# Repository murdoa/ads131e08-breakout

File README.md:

# ADS131E08 - Breakout

### Summary
Breakout board for bipolar 24-bit 8 channel simultaneous sampling ADC. 
Boards are daisy chainable for expanded inputs up to 128 input. Input range +/- 2.4V. PMOD compatible SPI Interface.

#### Features:
 - Daisy Chainable Design
 - External Clock Input
 - Configurble Active / Passive Frontend
 - Frontend Op-amps TLV4333 - 2uV Vos, 0.02 uV/C
 - Input Range -2.4V to 2.4V
 - Resolution 24 bit
 - Max sampling speeds 8ksps @ 24 bit, 32 ksps @ 16 bit
 
## Rendered Board

## Silkscreen and Component Layout

## Copper Layers
| Top Copper | Bottom Copper |
|:----:|:----:|
||  |

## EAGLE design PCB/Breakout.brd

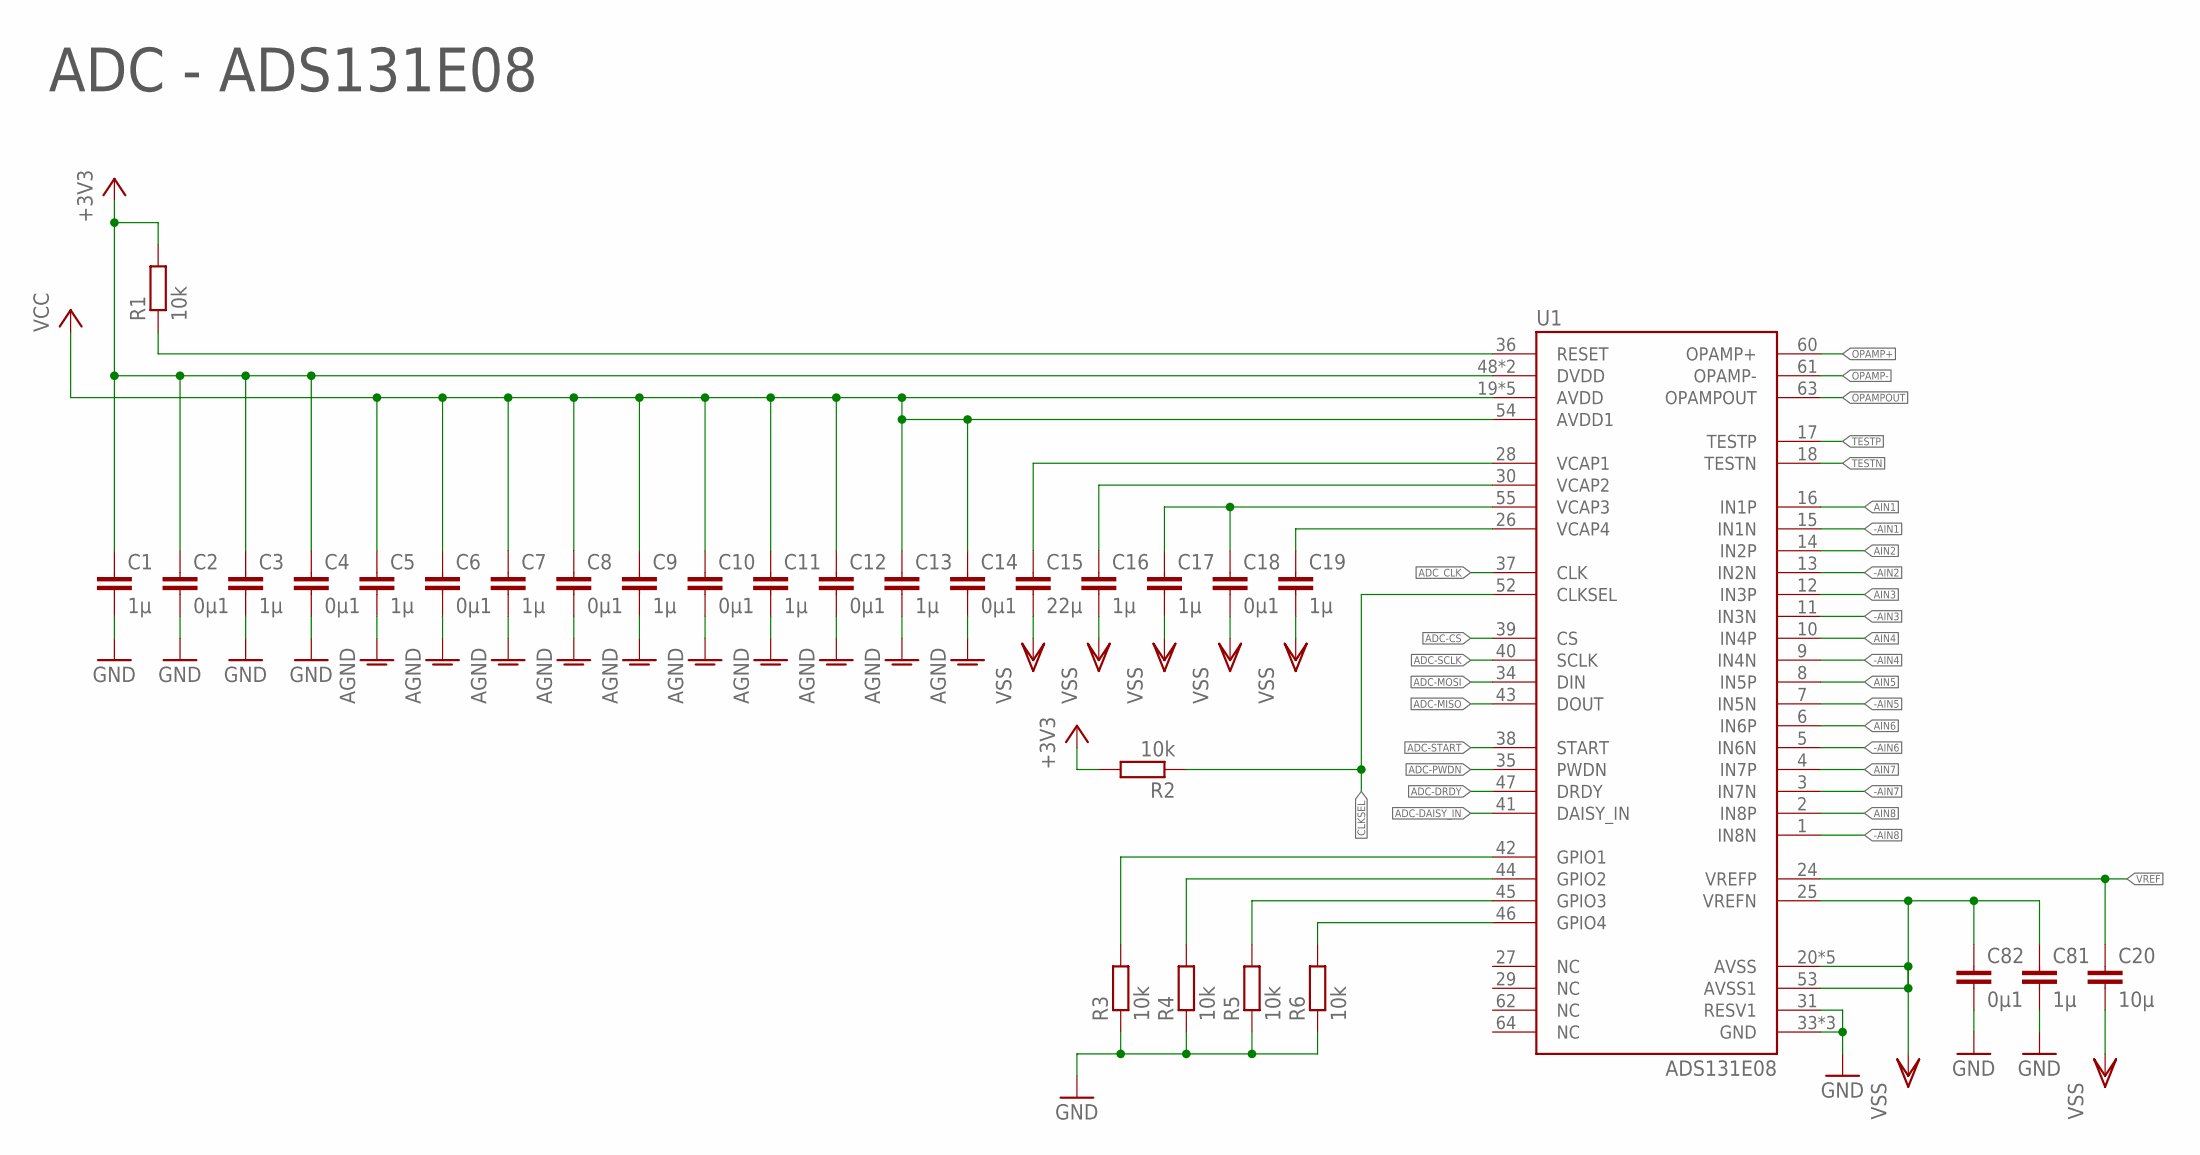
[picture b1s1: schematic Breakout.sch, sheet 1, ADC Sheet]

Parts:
C1, C3, C5, C7, C9, C11, C13, C16, C17, C19, C81: 1µ; C0603
C2, C4, C6, C8, C10, C12, C14, C18, C82: 0µ1; C0603
C15: 22µ; C0603
C20: 10µ; C0603
R1, R2, R3, R4, R5, R6: 10k; R0603
U1: ADS131E08; TQFP-64

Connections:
+3V3: C1.1, C2.1, C3.1, C4.1, R1.2, R2.2, U1.48 (DVDD), U1.50 (DVDD); also elsewhere on the board
-AIN1: U1.15 (IN1N); also elsewhere on the board
-AIN2: U1.13 (IN2N); also elsewhere on the board
-AIN3: U1.11 (IN3N); also elsewhere on the board
-AIN4: U1.9 (IN4N); also elsewhere on the board
-AIN5: U1.7 (IN5N); also elsewhere on the board
-AIN6: U1.5 (IN6N); also elsewhere on the board
-AIN7: U1.3 (IN7N); also elsewhere on the board
-AIN8: U1.1 (IN8N); also elsewhere on the board
ADC-CS: U1.39 (CS); also elsewhere on the board
ADC-DAISY_IN: U1.41 (DAISY_IN); also elsewhere on the board
ADC-DRDY: U1.47 (DRDY); also elsewhere on the board
ADC-MISO: U1.43 (DOUT); also elsewhere on the board
ADC-MOSI: U1.34 (DIN); also elsewhere on the board
ADC-PWDN: U1.35 (PWDN); also elsewhere on the board
ADC-RST: R1.1, U1.36 (RESET); also elsewhere on the board
ADC-SCLK: U1.40 (SCLK); also elsewhere on the board
ADC-START: U1.38 (START); also elsewhere on the board
ADC_CLK: U1.37 (CLK); also elsewhere on the board
AIN1: U1.16 (IN1P); also elsewhere on the board
AIN2: U1.14 (IN2P); also elsewhere on the board
AIN3: U1.12 (IN3P); also elsewhere on the board
AIN4: U1.10 (IN4P); also elsewhere on the board
AIN5: U1.8 (IN5P); also elsewhere on the board
AIN6: U1.6 (IN6P); also elsewhere on the board
AIN7: U1.4 (IN7P); also elsewhere on the board
AIN8: U1.2 (IN8P); also elsewhere on the board
CLKSEL: R2.1, U1.52 (CLKSEL)
GND: C1.2, C2.2, C3.2, C4.2, C5.2, C6.2, C7.2, C8.2, C9.2, C10.2, C11.2, C12.2, C13.2, C14.2, C81.2, C82.2, R3.1, R4.1, R5.1, R6.1, U1.31 (RESV1), U1.33 (GND), U1.49 (GND), U1.51 (GND); also elsewhere on the board
GPIO1: R3.2, U1.42 (GPIO1); also elsewhere on the board
GPIO2: R4.2, U1.44 (GPIO2)
GPIO3: R5.2, U1.45 (GPIO3)
GPIO4: R6.2, U1.46 (GPIO4)
OPAMP+: U1.60 (OPAMP+)
OPAMP-: U1.61 (OPAMP-)
OPAMPOUT: U1.63 (OPAMPOUT)
TESTN: U1.18 (TESTN)
TESTP: U1.17 (TESTP)
VCAP1: C15.1, U1.28 (VCAP1)
VCAP2: C16.1, U1.30 (VCAP2)
VCAP3: C17.1, C18.1, U1.55 (VCAP3)
VCAP4: C19.1, U1.26 (VCAP4)
VCC: C5.1, C6.1, C7.1, C8.1, C9.1, C10.1, C11.1, C12.1, C13.1, C14.1, U1.19 (AVDD), U1.21 (AVDD), U1.22 (AVDD), U1.54 (AVDD1), U1.56 (AVDD), U1.59 (AVDD); also elsewhere on the board
VREF: C20.1, U1.24 (VREFP); also elsewhere on the board
VSS: C15.2, C16.2, C17.2, C18.2, C19.2, C20.2, C81.1, C82.1, U1.20 (AVSS), U1.23 (AVSS), U1.25 (VREFN), U1.32 (AVSS), U1.53 (AVSS1), U1.57 (AVSS), U1.58 (AVSS); also elsewhere on the board

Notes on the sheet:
ADC - ADS131E08

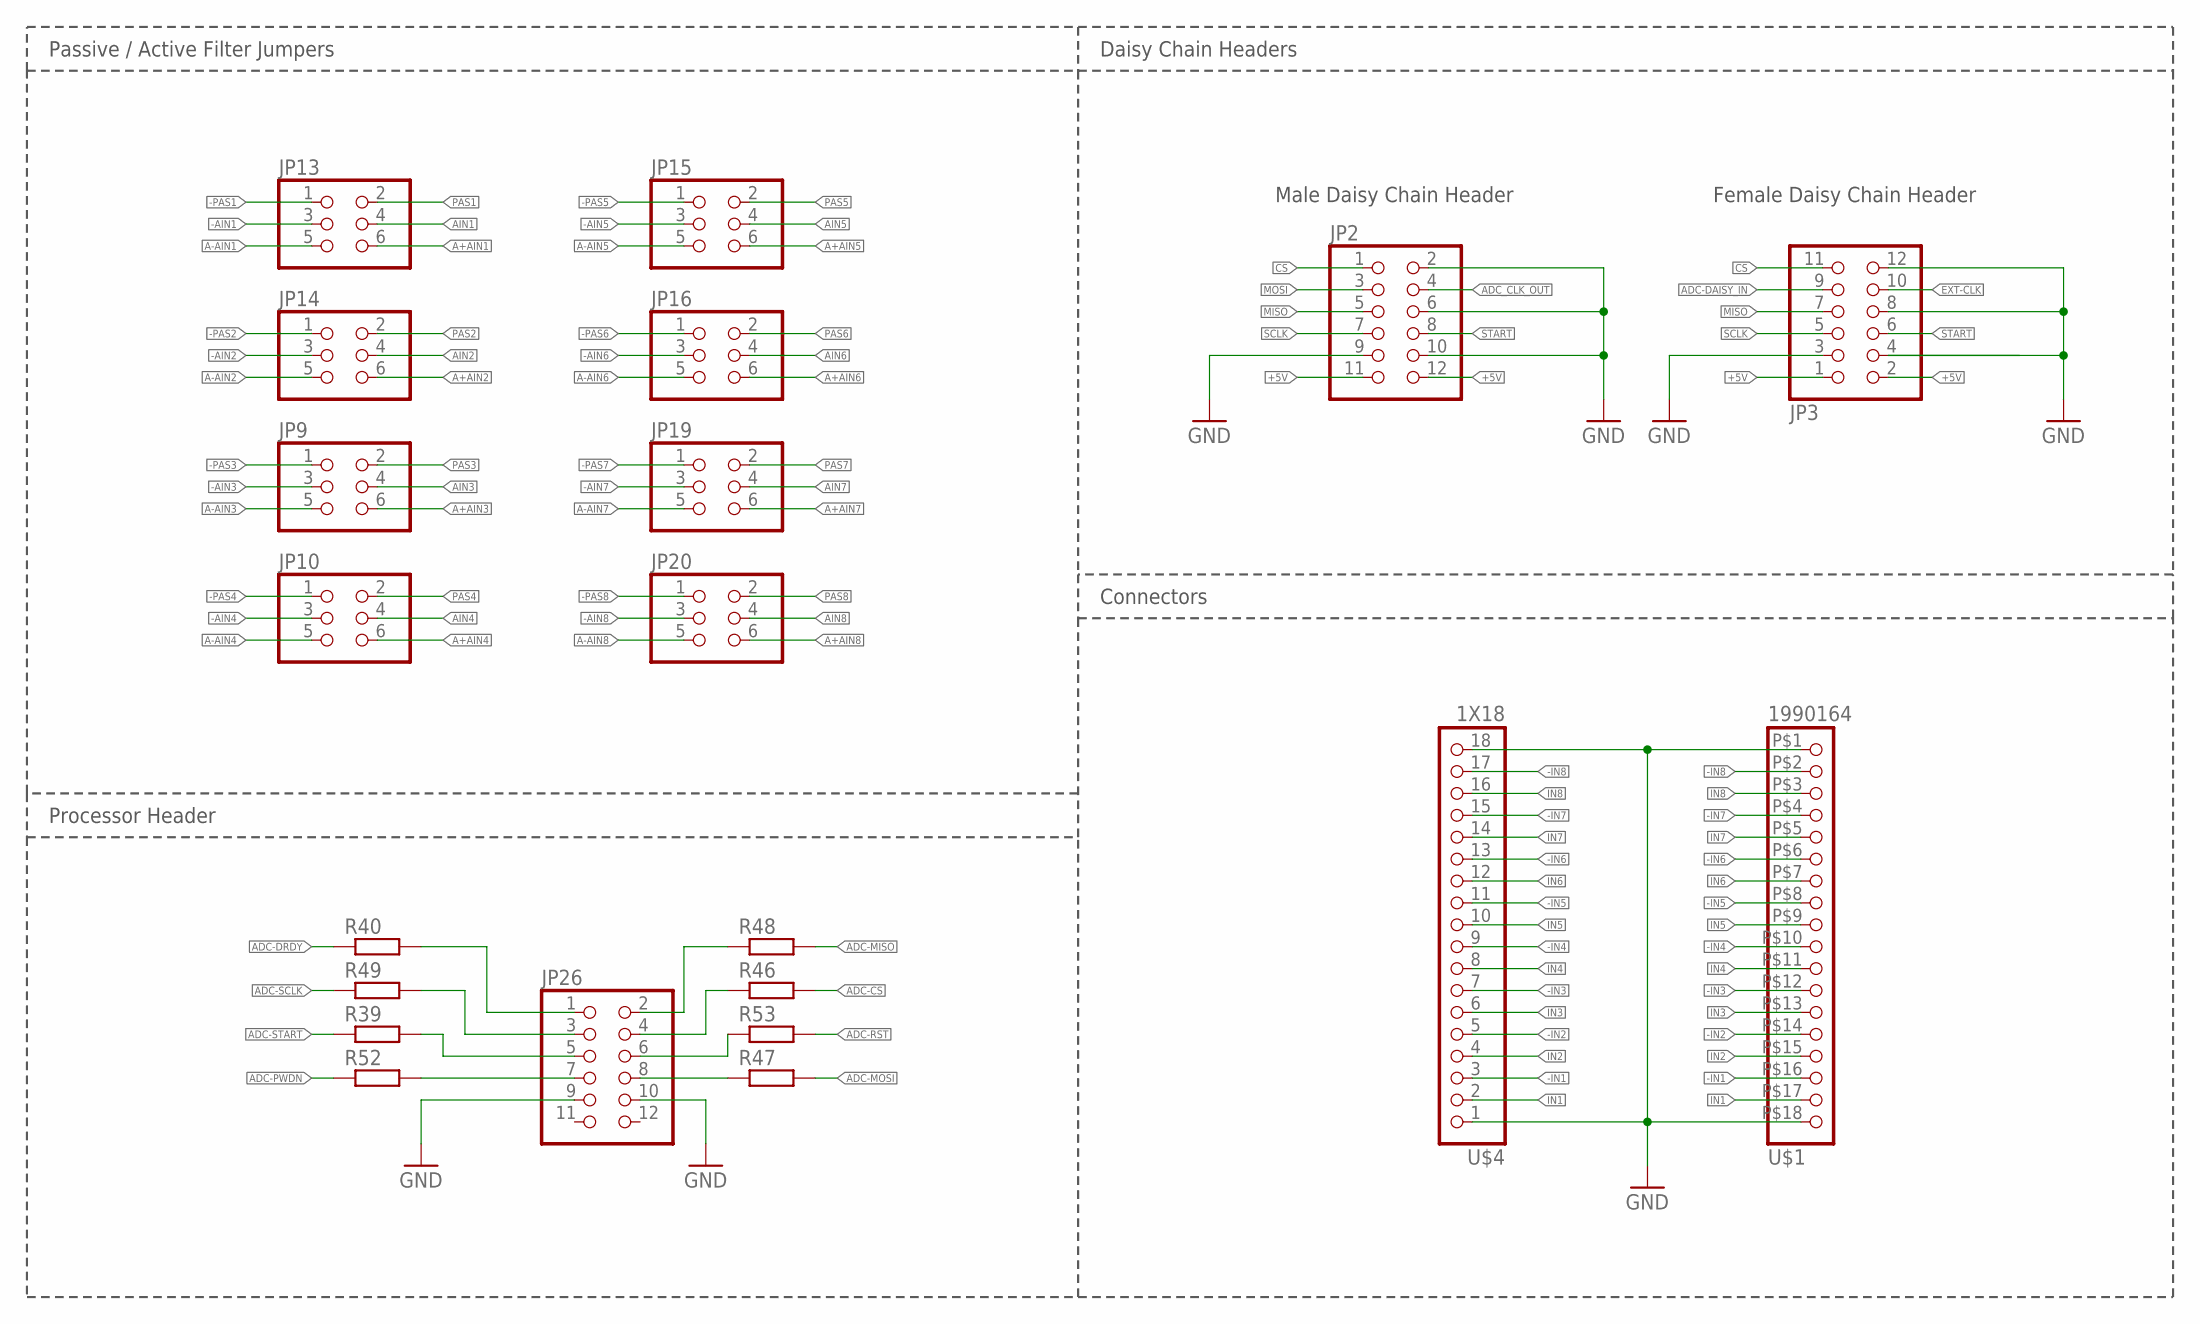
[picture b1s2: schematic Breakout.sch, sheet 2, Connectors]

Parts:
JP2, JP3, JP26: PINHD-2X6/90; 2X06/90
JP9, JP10, JP13, JP14, JP15, JP16, JP19, JP20: PINHD-2X3; 2X03
R39, R40, R46, R47, R48, R49, R52, R53: R-EU_R0603; R0603
U$1: 1990164; PTSA-2.5-Z
U$4: 1X18; 1X18/90

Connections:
+5V: JP2.11, JP2.12, JP3.1, JP3.2; also elsewhere on the board
-AIN1: JP13.3; also elsewhere on the board
-AIN2: JP14.3; also elsewhere on the board
-AIN3: JP9.3; also elsewhere on the board
-AIN4: JP10.3; also elsewhere on the board
-AIN5: JP15.3; also elsewhere on the board
-AIN6: JP16.3; also elsewhere on the board
-AIN7: JP19.3; also elsewhere on the board
-AIN8: JP20.3; also elsewhere on the board
-IN1: U$1.P$16 (3), U$4.3; also elsewhere on the board
-IN2: U$1.P$14 (5), U$4.5; also elsewhere on the board
-IN3: U$1.P$12 (7), U$4.7; also elsewhere on the board
-IN4: U$1.P$10 (9), U$4.9; also elsewhere on the board
-IN5: U$1.P$8 (11), U$4.11; also elsewhere on the board
-IN6: U$1.P$6 (13), U$4.13; also elsewhere on the board
-IN7: U$1.P$4 (15), U$4.15; also elsewhere on the board
-IN8: U$1.P$2 (17), U$4.17; also elsewhere on the board
-PAS1: JP13.1; also elsewhere on the board
-PAS2: JP14.1; also elsewhere on the board
-PAS3: JP9.1; also elsewhere on the board
-PAS4: JP10.1; also elsewhere on the board
-PAS5: JP15.1; also elsewhere on the board
-PAS6: JP16.1; also elsewhere on the board
-PAS7: JP19.1; also elsewhere on the board
-PAS8: JP20.1; also elsewhere on the board
A+AIN1: JP13.6; also elsewhere on the board
A+AIN2: JP14.6; also elsewhere on the board
A+AIN3: JP9.6; also elsewhere on the board
A+AIN4: JP10.6; also elsewhere on the board
A+AIN5: JP15.6; also elsewhere on the board
A+AIN6: JP16.6; also elsewhere on the board
A+AIN7: JP19.6; also elsewhere on the board
A+AIN8: JP20.6; also elsewhere on the board
A-AIN1: JP13.5; also elsewhere on the board
A-AIN2: JP14.5; also elsewhere on the board
A-AIN3: JP9.5; also elsewhere on the board
A-AIN4: JP10.5; also elsewhere on the board
A-AIN5: JP15.5; also elsewhere on the board
A-AIN6: JP16.5; also elsewhere on the board
A-AIN7: JP19.5; also elsewhere on the board
A-AIN8: JP20.5; also elsewhere on the board
ADC-CS: R46.1; also elsewhere on the board
ADC-DAISY_IN: JP3.9; also elsewhere on the board
ADC-DRDY: R40.2; also elsewhere on the board
ADC-MISO: R48.1; also elsewhere on the board
ADC-MOSI: R47.1; also elsewhere on the board
ADC-PWDN: R52.2; also elsewhere on the board
ADC-RST: R53.2; also elsewhere on the board
ADC-SCLK: R49.1; also elsewhere on the board
ADC-START: R39.2; also elsewhere on the board
ADC_CLK_OUT: JP2.4; also elsewhere on the board
AIN1: JP13.4; also elsewhere on the board
AIN2: JP14.4; also elsewhere on the board
AIN3: JP9.4; also elsewhere on the board
AIN4: JP10.4; also elsewhere on the board
AIN5: JP15.4; also elsewhere on the board
AIN6: JP16.4; also elsewhere on the board
AIN7: JP19.4; also elsewhere on the board
AIN8: JP20.4; also elsewhere on the board
CS: JP2.1, JP3.11, JP26.4, R46.2
DRDY: JP26.1, R40.1
EXT-CLK: JP3.10; also elsewhere on the board
GND: JP2.2, JP2.6, JP2.9, JP2.10, JP3.3, JP3.4, JP3.8, JP3.12, JP26.9, JP26.10, U$1.P$1 (18), U$1.P$18 (1), U$4.1, U$4.18; also elsewhere on the board
IN1: U$1.P$17 (2), U$4.2; also elsewhere on the board
IN2: U$1.P$15 (4), U$4.4; also elsewhere on the board
IN3: U$1.P$13 (6), U$4.6; also elsewhere on the board
IN4: U$1.P$11 (8), U$4.8; also elsewhere on the board
IN5: U$1.P$9 (10), U$4.10; also elsewhere on the board
IN6: U$1.P$7 (12), U$4.12; also elsewhere on the board
IN7: U$1.P$5 (14), U$4.14; also elsewhere on the board
IN8: U$1.P$3 (16), U$4.16; also elsewhere on the board
MISO: JP2.5, JP3.7, JP26.2, R48.2
MOSI: JP2.3, JP26.8, R47.2
PAS1: JP13.2; also elsewhere on the board
PAS2: JP14.2; also elsewhere on the board
PAS3: JP9.2; also elsewhere on the board
PAS4: JP10.2; also elsewhere on the board
PAS5: JP15.2; also elsewhere on the board
PAS6: JP16.2; also elsewhere on the board
PAS7: JP19.2; also elsewhere on the board
PAS8: JP20.2; also elsewhere on the board
PWDN: JP26.7, R52.1
RST: JP26.6, R53.1
SCLK: JP2.7, JP3.5, JP26.3, R49.2
START: JP2.8, JP3.6, JP26.5, R39.1

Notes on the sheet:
Processor Header
Male Daisy Chain Header
Female Daisy Chain Header
Passive / Active Filter Jumpers
Daisy Chain Headers
Connectors

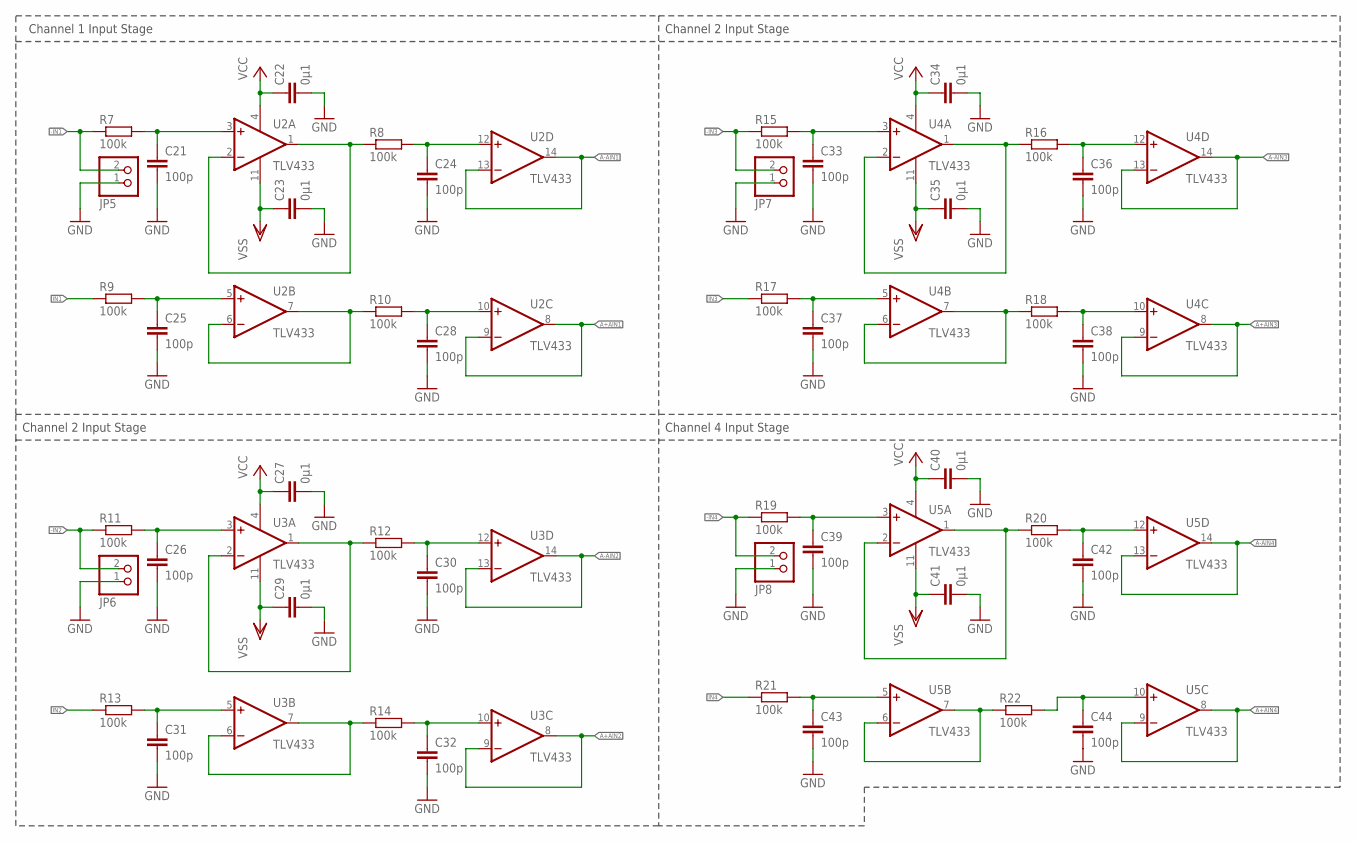
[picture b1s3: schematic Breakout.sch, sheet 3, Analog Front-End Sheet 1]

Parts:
C21, C24, C25, C26, C28, C30, C31, C32, C33, C36, C37, C38, C39, C42, C43, C44: 100p; C0603
C22, C23, C27, C29, C34, C35, C40, C41: 0µ1; C0603
JP5, JP6, JP7, JP8: PINHD-1X2; 1X02
R7, R8, R9, R10, R11, R12, R13, R14, R15, R16, R17, R18, R19, R20, R21, R22: 100k; R0603
U2, U3, U4, U5: TLV433; TSSOP14

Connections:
-IN1: JP5.2, R7.1; also elsewhere on the board
-IN2: JP6.2, R11.1; also elsewhere on the board
-IN3: JP7.2, R15.1; also elsewhere on the board
-IN4: JP8.2, R19.1; also elsewhere on the board
-PAS1: C21.1, R7.2, U2.3 (+IN); also elsewhere on the board
-PAS2: C26.1, R11.2, U3.3 (+IN); also elsewhere on the board
-PAS3: C33.1, R15.2, U4.3 (+IN); also elsewhere on the board
-PAS4: C39.1, R19.2, U5.3 (+IN); also elsewhere on the board
A+AIN1: U2.8 (OUT), U2.9 (-IN); also elsewhere on the board
A+AIN2: U3.8 (OUT), U3.9 (-IN); also elsewhere on the board
A+AIN3: U4.8 (OUT), U4.9 (-IN); also elsewhere on the board
A+AIN4: U5.8 (OUT), U5.9 (-IN); also elsewhere on the board
A-AIN1: U2.13 (-IN), U2.14 (OUT); also elsewhere on the board
A-AIN2: U3.13 (-IN), U3.14 (OUT); also elsewhere on the board
A-AIN3: U4.13 (-IN), U4.14 (OUT); also elsewhere on the board
A-AIN4: U5.13 (-IN), U5.14 (OUT); also elsewhere on the board
GND: C21.2, C22.2, C23.2, C24.2, C25.2, C26.2, C27.2, C28.2, C29.2, C30.2, C31.2, C32.2, C33.2, C34.2, C35.2, C36.2, C37.2, C38.2, C39.2, C40.2, C41.2, C42.2, C43.2, C44.2, JP5.1, JP6.1, JP7.1, JP8.1; also elsewhere on the board
IN1: R9.1; also elsewhere on the board
IN2: R13.1; also elsewhere on the board
IN3: R17.1; also elsewhere on the board
IN4: R21.1; also elsewhere on the board
unnamed: C36.1, R16.2, U4.12 (+IN)
unnamed: R16.1, U4.1 (OUT), U4.2 (-IN)
unnamed: C28.1, R10.2, U2.10 (+IN)
unnamed: C24.1, R8.2, U2.12 (+IN)
unnamed: R8.1, U2.1 (OUT), U2.2 (-IN)
unnamed: R10.1, U2.6 (-IN), U2.7 (OUT)
unnamed: C38.1, R18.2, U4.10 (+IN)
unnamed: C30.1, R12.2, U3.12 (+IN)
unnamed: R12.1, U3.1 (OUT), U3.2 (-IN)
unnamed: R18.1, U4.6 (-IN), U4.7 (OUT)
unnamed: C32.1, R14.2, U3.10 (+IN)
unnamed: R14.1, U3.6 (-IN), U3.7 (OUT)
unnamed: C42.1, R20.2, U5.12 (+IN)
unnamed: R20.1, U5.1 (OUT), U5.2 (-IN)
unnamed: C44.1, R22.2, U5.10 (+IN)
unnamed: R22.1, U5.6 (-IN), U5.7 (OUT)
PAS1: C25.1, R9.2, U2.5 (+IN); also elsewhere on the board
PAS2: C31.1, R13.2, U3.5 (+IN); also elsewhere on the board
PAS3: C37.1, R17.2, U4.5 (+IN); also elsewhere on the board
PAS4: C43.1, R21.2, U5.5 (+IN); also elsewhere on the board
VCC: C22.1, C27.1, C34.1, C40.1, U2.4 (V+), U3.4 (V+), U4.4 (V+), U5.4 (V+); also elsewhere on the board
VSS: C23.1, C29.1, C35.1, C41.1, U2.11 (V-), U3.11 (V-), U4.11 (V-), U5.11 (V-); also elsewhere on the board

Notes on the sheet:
Channel 1 Input Stage
Channel 2 Input Stage
Channel 4 Input Stage

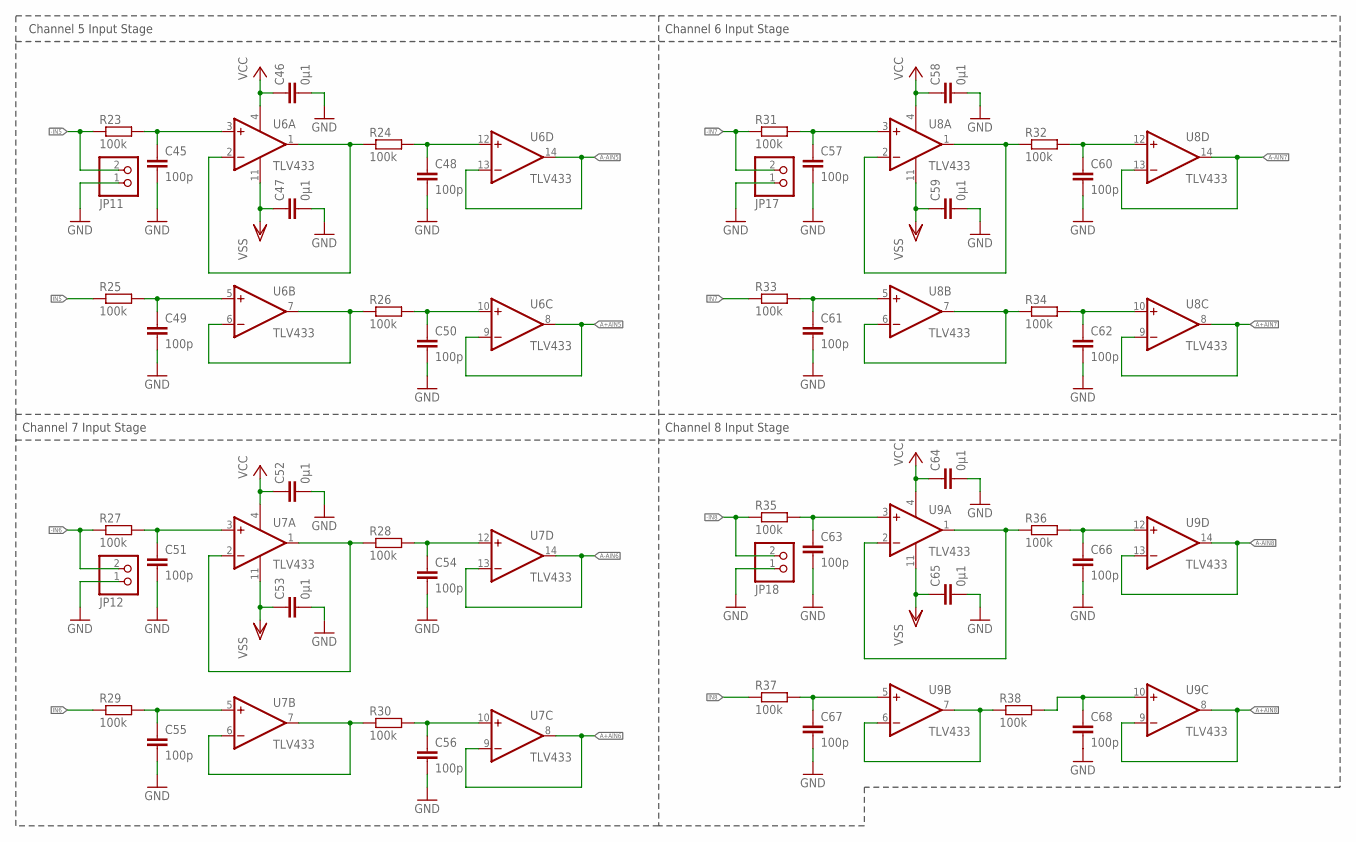
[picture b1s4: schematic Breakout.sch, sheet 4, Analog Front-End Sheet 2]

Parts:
C45, C48, C49, C50, C51, C54, C55, C56, C57, C60, C61, C62, C63, C66, C67, C68: 100p; C0603
C46, C47, C52, C53, C58, C59, C64, C65: 0µ1; C0603
JP11, JP12, JP17, JP18: PINHD-1X2; 1X02
R23, R24, R25, R26, R27, R28, R29, R30, R31, R32, R33, R34, R35, R36, R37, R38: 100k; R0603
U6, U7, U8, U9: TLV433; TSSOP14

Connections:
-IN5: JP11.2, R23.1; also elsewhere on the board
-IN6: JP12.2, R27.1; also elsewhere on the board
-IN7: JP17.2, R31.1; also elsewhere on the board
-IN8: JP18.2, R35.1; also elsewhere on the board
-PAS5: C45.1, R23.2, U6.3 (+IN); also elsewhere on the board
-PAS6: C51.1, R27.2, U7.3 (+IN); also elsewhere on the board
-PAS7: C57.1, R31.2, U8.3 (+IN); also elsewhere on the board
-PAS8: C63.1, R35.2, U9.3 (+IN); also elsewhere on the board
A+AIN5: U6.8 (OUT), U6.9 (-IN); also elsewhere on the board
A+AIN6: U7.8 (OUT), U7.9 (-IN); also elsewhere on the board
A+AIN7: U8.8 (OUT), U8.9 (-IN); also elsewhere on the board
A+AIN8: U9.8 (OUT), U9.9 (-IN); also elsewhere on the board
A-AIN5: U6.13 (-IN), U6.14 (OUT); also elsewhere on the board
A-AIN6: U7.13 (-IN), U7.14 (OUT); also elsewhere on the board
A-AIN7: U8.13 (-IN), U8.14 (OUT); also elsewhere on the board
A-AIN8: U9.13 (-IN), U9.14 (OUT); also elsewhere on the board
GND: C45.2, C46.2, C47.2, C48.2, C49.2, C50.2, C51.2, C52.2, C53.2, C54.2, C55.2, C56.2, C57.2, C58.2, C59.2, C60.2, C61.2, C62.2, C63.2, C64.2, C65.2, C66.2, C67.2, C68.2, JP11.1, JP12.1, JP17.1, JP18.1; also elsewhere on the board
IN5: R25.1; also elsewhere on the board
IN6: R29.1; also elsewhere on the board
IN7: R33.1; also elsewhere on the board
IN8: R37.1; also elsewhere on the board
unnamed: C48.1, R24.2, U6.12 (+IN)
unnamed: R24.1, U6.1 (OUT), U6.2 (-IN)
unnamed: C50.1, R26.2, U6.10 (+IN)
unnamed: R26.1, U6.6 (-IN), U6.7 (OUT)
unnamed: C54.1, R28.2, U7.12 (+IN)
unnamed: R28.1, U7.1 (OUT), U7.2 (-IN)
unnamed: C56.1, R30.2, U7.10 (+IN)
unnamed: R30.1, U7.6 (-IN), U7.7 (OUT)
unnamed: C60.1, R32.2, U8.12 (+IN)
unnamed: R32.1, U8.1 (OUT), U8.2 (-IN)
unnamed: C62.1, R34.2, U8.10 (+IN)
unnamed: R34.1, U8.6 (-IN), U8.7 (OUT)
unnamed: C66.1, R36.2, U9.12 (+IN)
unnamed: R36.1, U9.1 (OUT), U9.2 (-IN)
unnamed: C68.1, R38.2, U9.10 (+IN)
unnamed: R38.1, U9.6 (-IN), U9.7 (OUT)
PAS5: C49.1, R25.2, U6.5 (+IN); also elsewhere on the board
PAS6: C55.1, R29.2, U7.5 (+IN); also elsewhere on the board
PAS7: C61.1, R33.2, U8.5 (+IN); also elsewhere on the board
PAS8: C67.1, R37.2, U9.5 (+IN); also elsewhere on the board
VCC: C46.1, C52.1, C58.1, C64.1, U6.4 (V+), U7.4 (V+), U8.4 (V+), U9.4 (V+); also elsewhere on the board
VSS: C47.1, C53.1, C59.1, C65.1, U6.11 (V-), U7.11 (V-), U8.11 (V-), U9.11 (V-); also elsewhere on the board

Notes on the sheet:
Channel 5 Input Stage
Channel 7 Input Stage
Channel 6 Input Stage
Channel 8 Input Stage

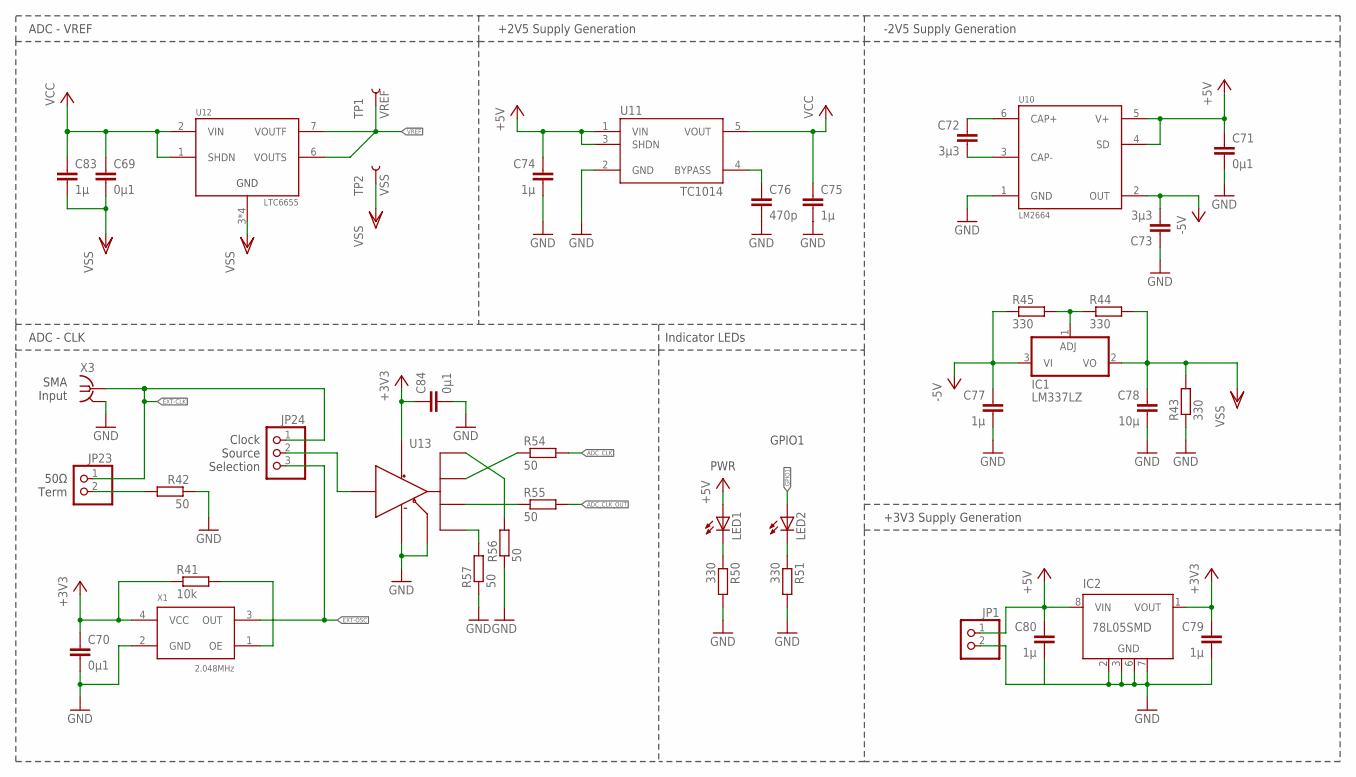
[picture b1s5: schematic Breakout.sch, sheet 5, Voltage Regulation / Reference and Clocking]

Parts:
C69, C70, C71, C84: 0µ1; C0603
C72, C73: 3µ3; C0805
C74, C75, C77, C79, C80: 1µ; C0805
C76: 470p; C0603
C78: 10µ; C0805
C83: 1µ; C0603
IC1: LM337LZ; TO92
IC2: 78L05SMD; SO08
JP1, JP23: PINHD-1X2; 1X02
JP24: PINHD-1X3; 1X03
LED1, LED2: LEDCHIP-LED0805; CHIP-LED0805
R41: 10k; R0603
R42, R54, R55, R56, R57: 50; R0603
R43, R44, R45, R50, R51: 330; R0603
TP1: VREF; PAD.03X.03
TP2: VSS; PAD.03X.03
U10: LM2664; SOT23-6
U11: TC1014; SOT23-5L
U12: LTC6655; LS8
U13: 74AVC9112GTX; XFDFN-8
X1: 2.048MHz; SG5032CAN
X3: BU-SMA-V

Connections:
+3V3: C70.1, C79.1, C84.1, IC2.1 (VOUT), R41.1, U13.P$1 (VCC), X1.4 (VCC); also elsewhere on the board
+5V: C71.1, C74.1, C80.1, IC2.8 (VIN), JP1.1, LED1.A, U10.4 (SD), U10.5 (V+), U11.1 (VIN), U11.3 (SHDN); also elsewhere on the board
-5V: C73.2, C77.1, IC1.3 (VI), R45.1, U10.2 (OUT)
ADC_CLK: R54.2; also elsewhere on the board
ADC_CLK_OUT: R55.2; also elsewhere on the board
EXT-CLK: JP23.1, JP24.1, X3.1; also elsewhere on the board
EXT-OSC: JP24.3, X1.3 (OUT)
GND: C70.2, C71.2, C73.1, C74.2, C75.2, C76.2, C77.2, C78.2, C79.2, C80.2, C84.2, IC2.2 (GND), IC2.3 (GND), IC2.6 (GND), IC2.7 (GND), JP1.2, R42.1, R43.1, R50.2, R51.2, R56.1, R57.1, U10.1 (GND), U11.2 (GND), U13.P$3 (OE), U13.P$4 (GND), X1.2 (GND), X3.2, X3.3 (2), X3.4 (2), X3.5 (2); also elsewhere on the board
GPIO1: LED2.A; also elsewhere on the board
unnamed: R41.2, X1.1 (OE)
unnamed: C72.1, U10.6 (CAP+)
unnamed: C72.2, U10.3 (CAP-)
unnamed: JP24.2, U13.P$2 (A)
unnamed: JP23.2, R42.2
unnamed: C76.1, U11.4 (BYPASS)
unnamed: IC1.1 (ADJ), R44.1, R45.2
unnamed: R54.1, U13.P$6 (Y2)
unnamed: R55.1, U13.P$7 (Y3)
unnamed: R56.2, U13.P$5 (Y1)
unnamed: R57.2, U13.P$8 (Y4)
unnamed: LED2.C, R51.1
unnamed: LED1.C, R50.1
VCC: C69.1, C75.1, C83.1, U11.5 (VOUT), U12.1 (SHDN), U12.2 (VIN); also elsewhere on the board
VREF: TP1.P$1, U12.6 (VOUTS), U12.7 (VOUTF); also elsewhere on the board
VSS: C69.2, C78.1, C83.2, IC1.2 (VO), R43.2, R44.2, TP2.P$1, U12.3 (GND), U12.4 (GND), U12.5 (GND), U12.8 (GND); also elsewhere on the board

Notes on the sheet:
PWR
GPIO1
ADC - VREF
+2V5 Supply Generation
ADC - CLK
50Ω Term
SMA Input
Clock Source Selection
-2V5 Supply Generation
Indicator LEDs
+3V3 Supply Generation

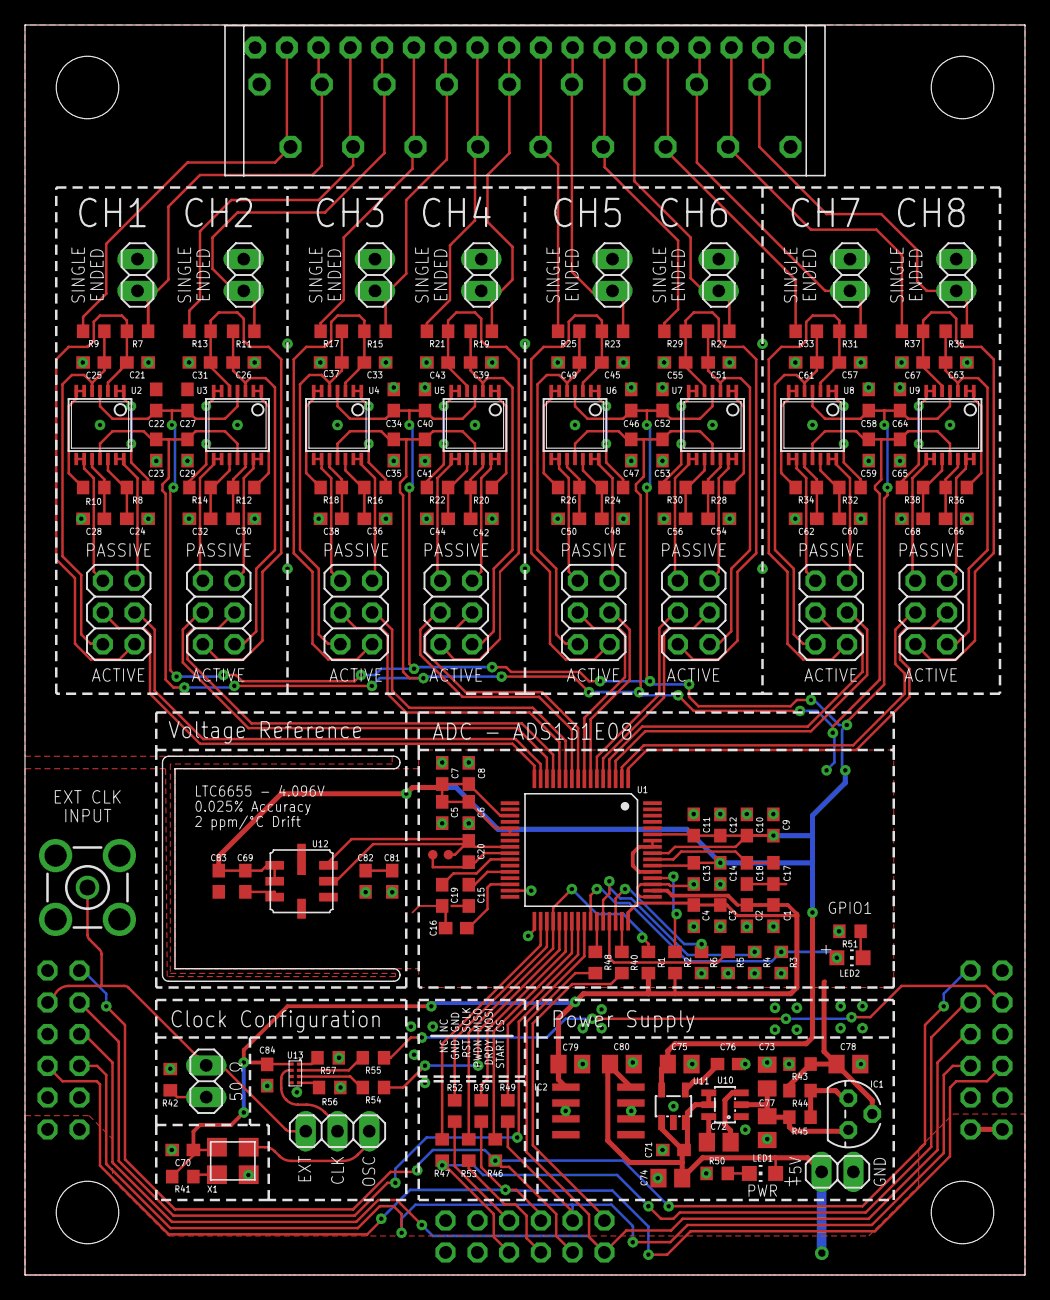
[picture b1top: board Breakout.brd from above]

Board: 2 copper layers, 79.9 x 99.9 mm, 186 parts (0 on the bottom side), 146 nets.

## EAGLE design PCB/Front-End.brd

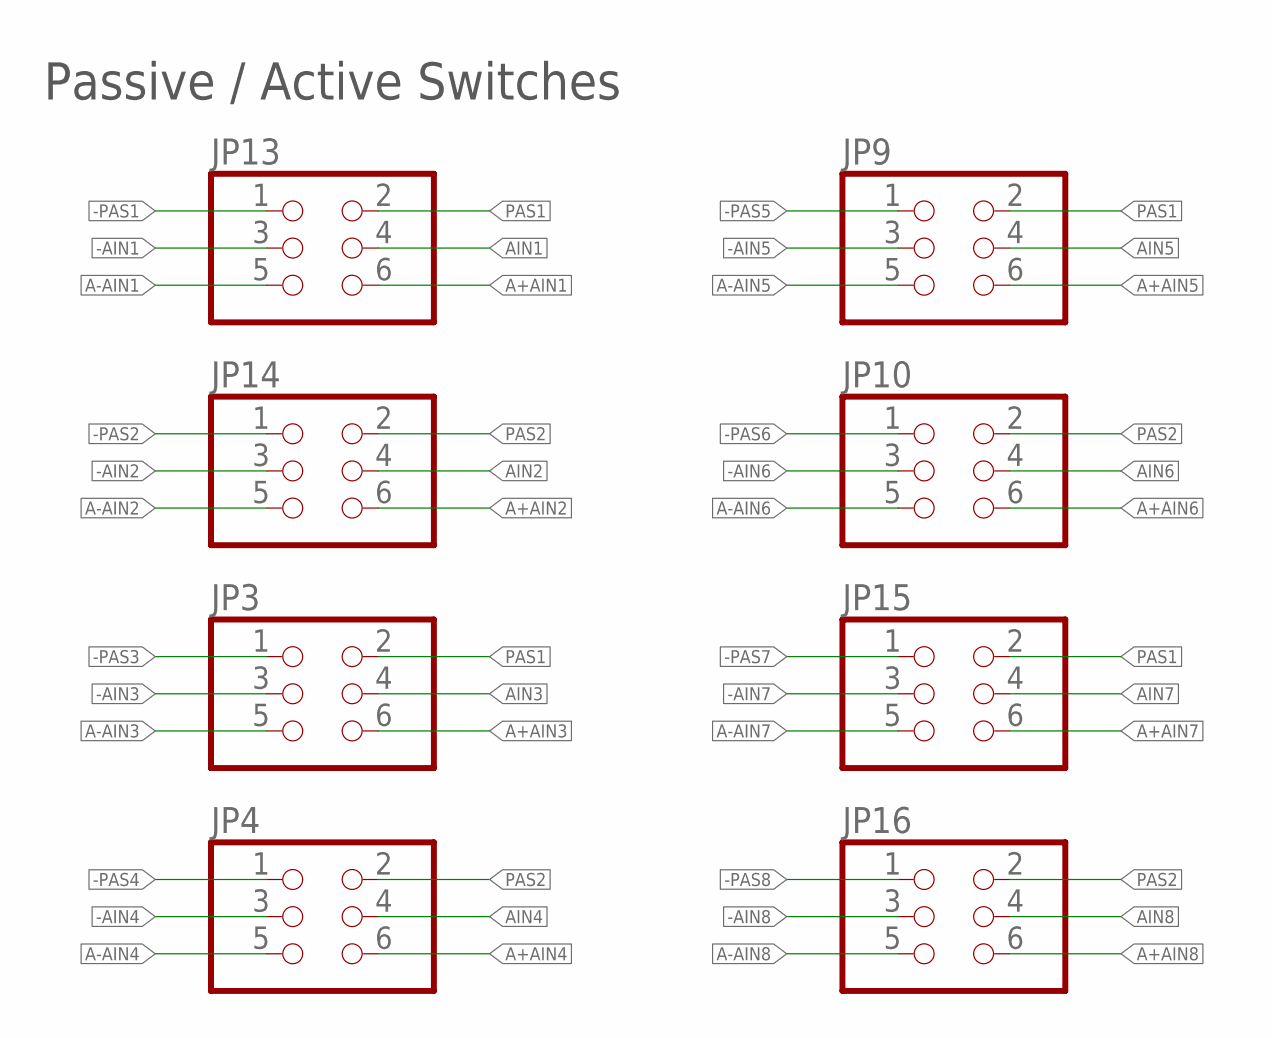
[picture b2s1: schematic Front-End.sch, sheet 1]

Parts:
JP3, JP4, JP9, JP10, JP13, JP14, JP15, JP16: PINHD-2X3; 2X03

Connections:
-AIN1: JP13.3
-AIN2: JP14.3
-AIN3: JP3.3
-AIN4: JP4.3
-AIN5: JP9.3
-AIN6: JP10.3
-AIN7: JP15.3
-AIN8: JP16.3
-PAS1: JP13.1; also elsewhere on the board
-PAS2: JP14.1; also elsewhere on the board
-PAS3: JP3.1; also elsewhere on the board
-PAS4: JP4.1; also elsewhere on the board
-PAS5: JP9.1; also elsewhere on the board
-PAS6: JP10.1; also elsewhere on the board
-PAS7: JP15.1; also elsewhere on the board
-PAS8: JP16.1; also elsewhere on the board
A+AIN1: JP13.6; also elsewhere on the board
A+AIN2: JP14.6; also elsewhere on the board
A+AIN3: JP3.6; also elsewhere on the board
A+AIN4: JP4.6; also elsewhere on the board
A+AIN5: JP9.6; also elsewhere on the board
A+AIN6: JP10.6; also elsewhere on the board
A+AIN7: JP15.6; also elsewhere on the board
A+AIN8: JP16.6; also elsewhere on the board
A-AIN1: JP13.5; also elsewhere on the board
A-AIN2: JP14.5; also elsewhere on the board
A-AIN3: JP3.5; also elsewhere on the board
A-AIN4: JP4.5; also elsewhere on the board
A-AIN5: JP9.5; also elsewhere on the board
A-AIN6: JP10.5; also elsewhere on the board
A-AIN7: JP15.5; also elsewhere on the board
A-AIN8: JP16.5; also elsewhere on the board
AIN1: JP13.4
AIN2: JP14.4
AIN3: JP3.4
AIN4: JP4.4
AIN5: JP9.4
AIN6: JP10.4
AIN7: JP15.4
AIN8: JP16.4
PAS1: JP3.2, JP9.2, JP13.2, JP15.2; also elsewhere on the board
PAS2: JP4.2, JP10.2, JP14.2, JP16.2; also elsewhere on the board

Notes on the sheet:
Passive / Active Switches

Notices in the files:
parts and their libraries:
SparkFun-Aesthetics: Licensing: Creative Commons ShareAlike 4.0 International - https://creativecommons.org/licenses/by-sa/4.0
